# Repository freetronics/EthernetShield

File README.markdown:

Freetronics Ethernet Shield for Arduino
=======================================
Copyright 2010 Jonathan Oxer <jon@freetronics.com>  
Practical Arduino: <www.practicalarduino.com>  
Freetronics: <www.freetronics.com>

************************************************************************
** WARNING: THIS IS A WORK IN PROGRESS AND PROBABLY BROKEN RIGHT NOW. **
** DON'T TRY TO FAB THIS BOARD OR IT WILL BE A WASTE OF TIME / MONEY! **
************************************************************************

10/100base-T Ethernet shield for the Arduino Duemilanove microcontroller
and other boards based on the same header format, such as the TwentyTen,
the Seeeduino, and the Arduino Pro.

Includes significant prototyping area using the spare shield area.

Features:

 * Reset button wired through to Arduino reset pin.
 * Parts overlay on both the top and the bottom so you can see what you
   are connecting without turning the board over.

INSTALLATION
------------
The design is saved as an EAGLE project. EAGLE PCB design software is
available from www.cadsoftusa.com free for non-commercial use. To use
this project download it and place the directory containing these files
into the "eagle" directory on your computer. Then open EAGLE and
navigate to Projects -> eagle -> ProtoShield.

LICENSE
-------
Licensed under the TAPR Open Hardware License (www.tapr.org/OHL).

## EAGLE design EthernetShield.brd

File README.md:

Freetronics Ethernet Shield
===========================
Copyright 2010-2012 Freetronics Pty Ltd  
Freetronics site:  www.freetronics.com  
Freetronics email: info@freetronics.com  

10/100base-T Ethernet shield for the Freetronics Eleven, Arduino Uno,
and other boards compatible with the R3 header format.

Includes significant prototyping area using the spare shield area, and
supports Power-over-Ethernet (PoE) using either simple jumpers for DIY
PoE or a daughter-board module for full standards-compliant PoE.

Features:

 * Prototyping area.
 * 10/100Base-T connectivity.
 * Power-over-Ethernet "PD" (powered device) support.
 * Activity / status indicators.
 * Reset button wired through to Arduino reset pin.
 * Wiznet W5100 IC reset circuit.
 * SPI bus contention fixed for W5100 IC.
 * Parts overlay on both the top and the bottom.

More information is available on our product page at:

  http://www.freetronics.com/ethernet

The "docs" folder within this repository includes a handy copy of the
schematic in PDF format and image(s) of the pcb.

INSTALLATION
------------
The design is saved as an EAGLE project. EAGLE PCB design software is
available from www.cadsoftusa.com free for non-commercial use. To use
this project download it and place the directory containing these files
into the "eagle" directory on your computer. Then open EAGLE and
navigate to Projects -> eagle -> EthernetShieldR3.

DISTRIBUTION
------------
The specific terms of distribution of this project are governed by the
license referenced below.

LICENSE
-------
Licensed under the TAPR Open Hardware License (www.tapr.org/OHL).
The "license" folder within this repository also contains a copy of
this license in plain text format.

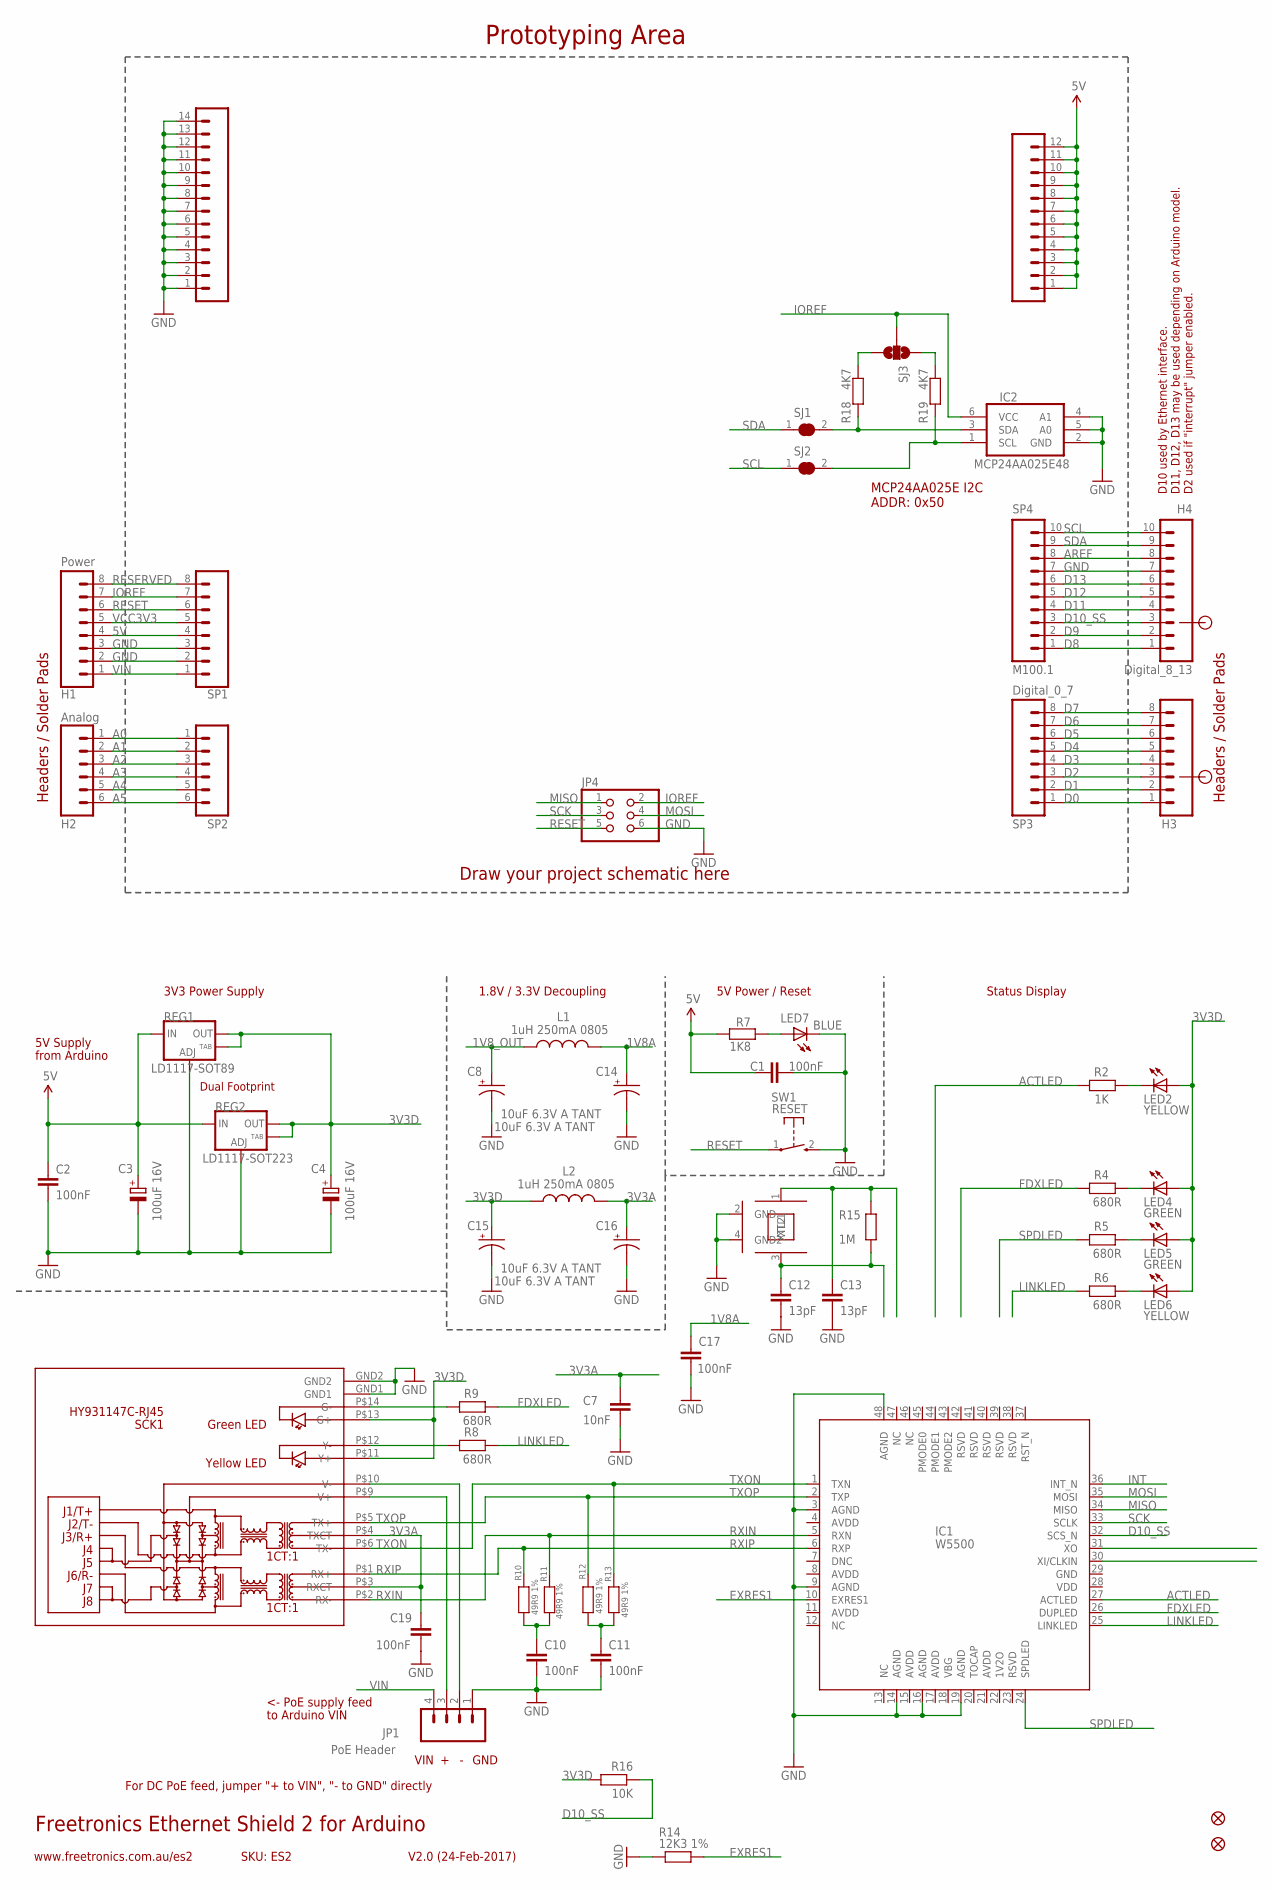
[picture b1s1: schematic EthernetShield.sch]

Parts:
C1, C2, C10, C11, C17, C19: 100nF; 0603
C3, C4: 100uF 16V; PANASONIC_D
C7: 10nF; 0603
C8, C14, C15, C16: 10uF 6.3V A TANT; EIA3216
C12, C13: 13pF; 0603
H1: Power; 1X08
H2: Analog; 1X06
H3: Digital_0_7; 1X08
H4: Digital_8_13; 1X10
IC1: W5500
IC2: MCP24AA025E48; SOT23-6
JP1: PoE Header; 1X04
JP4: PINHD-2X3; 2X03
L1, L2: 1uH 250mA 0805; L2012C
LED2, LED6: YELLOW; LED-0603
LED4, LED5: GREEN; LED-0603
LED7: BLUE; LED-0603
PADS_5V: M12PTH; 1X12
PADS_GND: M14; 1X14
R2: 1K; 0603
R4, R5, R6, R8, R9: 680R; 0603
R7: 1K8; 0603
R10, R11, R12, R13: 49R9 1%; 0603
R14: 12K3 1%; 0603
R15: 1M; 0603
R16: 10K; 0603
R18, R19: 4K7; 0603
REG1: LD1117-SOT89; SOT89
REG2: LD1117-SOT223; SOT223
SCK1: HY931147C-RJ45; HY931147C
SJ1, SJ2: SJCN; SJC
SJ3: SOLDERJUMPER_2WAYT; SJ_2
SP1: M08; 1X08
SP2: Analog; 1X06
SP3: Digital_0_7; 1X08
SP4: M100.1; 1X10
SW1: RESET; TACTILE_SWITCH_SMD_2PIN_TINY
U$6, U$8: FIDUCIAL1X2.5; FIDUCIAL-1X2.5
XTL1: 25MHZ; CRYSTAL-SMD-3X2

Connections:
1V8A: C14.A (+), C17.1, L1.2
1V8_OUT: C8.A (+), L1.1
3V3A: C7.1, C16.A (+), C19.1, L2.2, SCK1.P$3 (RXCT), SCK1.P$4 (TXCT)
3V3D: C4.+, C15.A (+), L2.1, LED2.A, LED4.A, LED5.A, LED6.A, R16.2, REG1.2 (OUT), REG1.4 (OUT), REG2.2 (OUT), REG2.4 (OUT), SCK1.P$11 (Y+), SCK1.P$13 (G+)
5V: C1.1, C2.1, C3.+, H1.4, PADS_5V.1, PADS_5V.2, PADS_5V.3, PADS_5V.4, PADS_5V.5, PADS_5V.6, PADS_5V.7, PADS_5V.8, PADS_5V.9, PADS_5V.10, PADS_5V.11, PADS_5V.12, R7.1, REG1.3 (IN), REG2.3 (IN), SP1.4
A0: H2.1, SP2.1
A1: H2.2, SP2.2
A2: H2.3, SP2.3
A3: H2.4, SP2.4
A4: H2.5, SP2.5
A5: H2.6, SP2.6
ACTLED: IC1.27 (ACTLED), R2.2
AREF: H4.8, SP4.8
D0: H3.1, SP3.1
D1: H3.2, SP3.2
D2: H3.3, SP3.3
D3: H3.4, SP3.4
D4: H3.5, SP3.5
D5: H3.6, SP3.6
D6: H3.7, SP3.7
D7: H3.8, SP3.8
D8: H4.1, SP4.1
D9: H4.2, SP4.2
D10_SS: H4.3, IC1.32 (SCS_N), R16.1, SP4.3
D11: H4.4, SP4.4
D12: H4.5, SP4.5
D13: H4.6, SP4.6
EXRES1: IC1.10 (EXRES1), R14.2
FDXLED: IC1.26 (DUPLED), R4.2, R9.1
GND: C1.2, C2.2, C3.-, C4.-, C7.2, C8.C (-), C10.2, C11.2, C12.2, C13.2, C14.C (-), C15.C (-), C16.C (-), C17.2, C19.2, H1.2, H1.3, H4.7, IC1.3 (AGND), IC1.9 (AGND), IC1.14 (AGND), IC1.16 (AGND), IC1.19 (AGND), IC1.48 (AGND), IC2.2 (GND), IC2.4 (A1), IC2.5 (A0), JP1.1, JP4.6, LED7.C, PADS_GND.1, PADS_GND.2, PADS_GND.3, PADS_GND.4, PADS_GND.5, PADS_GND.6, PADS_GND.7, PADS_GND.8, PADS_GND.9, PADS_GND.10, PADS_GND.11, PADS_GND.12, PADS_GND.13, PADS_GND.14, R14.1, REG1.1 (ADJ), REG2.1 (ADJ), SCK1.GND1, SCK1.GND2, SP1.2, SP1.3, SP4.7, SW1.2 (S), XTL1.2 (GND), XTL1.4 (GND2)
INT: IC1.36 (INT_N)
IOREF: H1.7, IC2.6 (VCC), JP4.2, SJ3.2, SP1.7
LINKLED: IC1.25 (LINKLED), R6.2, R8.1
MISO: IC1.34 (MISO), JP4.1
MOSI: IC1.35 (MOSI), JP4.4
unnamed: C11.1, R12.1, R13.2
unnamed: IC2.1 (SCL), R19.2, SJ2.2
unnamed: IC2.3 (SDA), R18.2, SJ1.2
unnamed: R18.1, SJ3.3
unnamed: R19.1, SJ3.1
unnamed: R9.2, SCK1.P$14 (G-)
unnamed: JP1.3, SCK1.P$9 (V+)
unnamed: JP1.2, SCK1.P$10 (V-)
unnamed: LED7.A, R7.2
unnamed: C10.1, R10.1, R11.2
unnamed: LED5.C, R5.1
unnamed: LED6.C, R6.1
unnamed: LED4.C, R4.1
unnamed: LED2.C, R2.1
unnamed: R8.2, SCK1.P$12 (Y-)
RESERVED: H1.8, SP1.8
RESET: H1.6, JP4.5, SP1.6, SW1.1
RXIN: IC1.5 (RXN), R11.1, SCK1.P$2 (RX-)
RXIP: IC1.6 (RXP), R10.2, SCK1.P$1 (RX+)
SCK: IC1.33 (SCLK), JP4.3
SCL: H4.10, SJ2.1, SP4.10
SDA: H4.9, SJ1.1, SP4.9
SPDLED: IC1.24 (SPDLED), R5.2
TXON: IC1.1 (TXN), R13.1, SCK1.P$6 (TX-)
TXOP: IC1.2 (TXP), R12.2, SCK1.P$5 (TX+)
VCC3V3: H1.5, SP1.5
VIN: H1.1, JP1.4, SP1.1
XTLN: C13.1, R15.2, XTL1.1 (XTL1)
XTLP: C12.1, R15.1, XTL1.3 (XTL2)

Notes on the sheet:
Prototyping Area
Freetronics Ethernet Shield 2 for Arduino
V2.0 (24-Feb-2017)
www.freetronics.com.au/es2
SKU: ES2
3V3 Power Supply
Status Display
5V Power / Reset
Headers / Solder Pads
Dual Footprint
from Arduino
1.8V / 3.3V Decoupling
Draw your project schematic here
D10 used by Ethernet interface.
D2 used if "interrupt" jumper enabled.
VIN
GND
<- PoE supply feed
5V Supply
For DC PoE feed, jumper "+ to VIN", "- to GND" directly
to Arduino VIN
D11, D12, D13 may be used depending on Arduino model.
MCP24AA025E I2C ADDR: 0x50

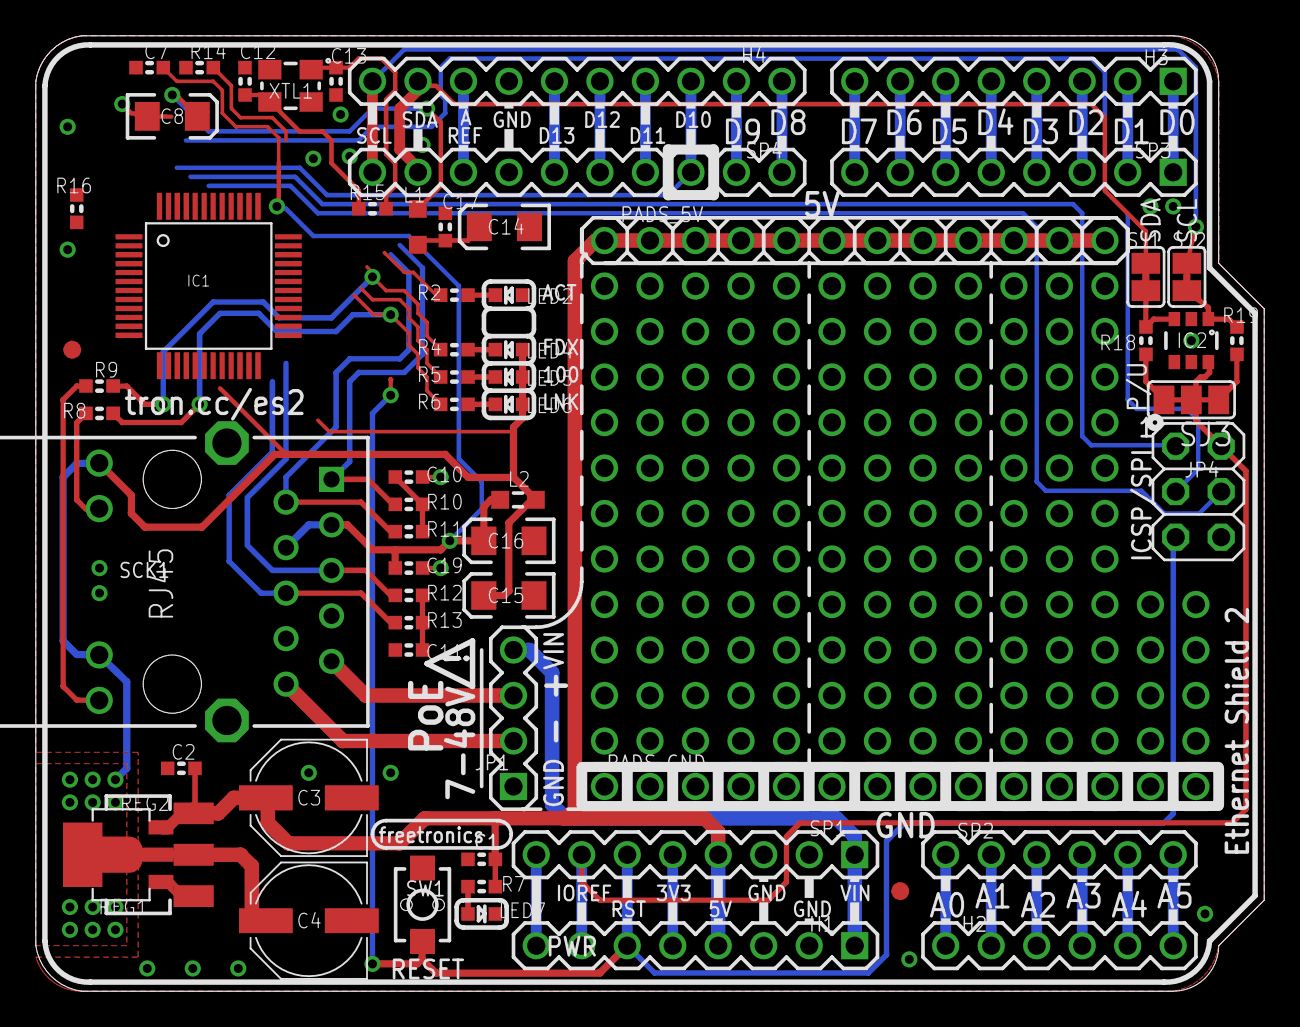
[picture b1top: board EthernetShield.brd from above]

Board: 2 copper layers, 68.6 x 53.3 mm, 62 parts (0 on the bottom side), 63 nets.

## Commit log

2010-04-27 Added initial version of Eagle files
2010-04-27 Added README
2010-04-27 Fixed markup
2010-04-28 Minor routing tweaks and start of restructuring schematic
2010-04-29 The "It gets worse before it gets better" release! * Major restructuring of schematic to explicitly show connections rather than relying on net labels. * Switched INT solder header to a proper 2-pin 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
2010-04-29 Moved major schematic sections around trying to make a logical layout
2010-04-30 The "slightly less tragic than last time" release! * Major re-routing around top of IC to make things neater and use less vias. * Added fiducial markers for assembly bots. * Minor track moves to avoi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
2010-04-30 Tiny track tweak
2010-04-30 Added preview image
2010-04-30 Labelling tweaks
2010-04-30 Swapped several parts for custom library parts to improve footprints and symbols
2010-04-30 Replaced SOT89 variant of LD1117 with custom library part to improve footprint
2010-05-01 Replaced more parts with custom library parts to optimise footprints, and adjusted routing to suit
2010-05-06 Minor routing and schematic layout tweaks
2010-05-09 Adjusted LED dropper resistor values to balance brightness
2010-05-20 Renamed and numbered all parts sequentially
2010-05-21 Switched to Hanrun magjack so we can add PoE support
2010-05-21 Start of routing for Hanrun magjack, totally busted right now
2010-05-22 More routing. Very ugly and busted right now
2010-05-23 Finally got it routing OK. Still needs cleanup
2010-05-23 Removed obsolete preview image
2010-05-24 Updated PoE size on overlay
2010-05-24 Trivial routing tweak
2010-05-27 Added docs dir
2010-05-27 Added license files
2010-05-27 Converted line endings
2010-05-27 Renamed README
2010-05-28 Removed execute privs
2010-05-28 Adjusted README to match Freetronics standard formatting
2010-05-28 Trivial track angle tweaks
2010-06-01 Repositioned LEDs; added border to LEDs; tweaked PoE markings
2010-06-01 Updated part designators; tweaked track routing
2010-06-02 Restructured schematic into 2 virtual sheets to allow space for a template worksheet
2010-06-03 Improved layout around prototyping area and marked pins in use
2010-06-03 Minor routing tweaks
2010-06-03 The tiniest track tweak in the history of tweaks. But it mattered. Really. In some universe, at least.
2010-06-16 1V8 and 3V3 filter system, power feed revisions
2010-06-16 small mods, SEN and RESET control next
2010-06-17 SEN SPI fix and WIZRST auto/manual W5100 reset
2010-06-21 PCB layout rearrangement to suit - still routing
2010-06-27 Schematic ERC fixes, PCB rework
2010-06-27 PCB track connectivity complete, GND review pending
2010-06-28 Last few checks
2010-06-28 Footprint revisions
2010-06-29 Production Release
2010-06-29 Bottom overlay went to last minute tweak-town
2010-07-31 ES v1_1 full production release
2010-08-20 ES V1_1 production release (final - C5 47nF)
2010-08-30 Work in progress message removed
2013-09-09 Upgrade to R3 headers and add MAC address chip
2013-09-09 Updates for release v2.0
2014-08-03 Changed I2C pull-ups to use IOREF, and added isolation jumpers
2014-08-03 Added info about I2C address
2018-03-28 Began replacing W5100 with W5500

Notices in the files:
EthernetShield.brd:
(c) 2014 Freetronics Pty Ltd
parts and their libraries:
freetronics-original: Licensing: CC v3.0 Share-Alike You are welcome to use this library for commercial purposes.
